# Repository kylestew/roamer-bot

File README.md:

# roamer-bot

A small robotics learning platform built on the Pololu Romi chassis.

The current direction is a custom-core Studio Mission Rover: Romi chassis, custom MCU + motor-control PCB, laptop tether first, telemetry from day one, and no ROS in the core system until the low-level robot is understood.

# Current Direction

The project is moving from the original Romi 32U4 + Raspberry Pi + ROS approach toward a custom-core learning build:

- Treat the old implementation as historical/reference material.
- Use the Romi chassis as the mechanical target.
- Build a custom MCU + motor-control PCB that replaces the purchasable Pololu Romi control board.
- Keep the first version tethered to a laptop.
- Capture telemetry from day one.
- Keep ROS out of the core system until the custom board, telemetry, and motor-control loop are understood.

# Current Structure

- `hardware/`: active Rev A PCB and mechanical-constraint work.
- `firmware/`: active custom MCU firmware work.
- `host/`: active laptop tether, telemetry capture, and test tooling work.
- `legacy/old-romi/`: previous Romi 32U4 + Raspberry Pi + ROS implementation, kept only as reference.
- `docs/`: datasheets, Romi reference assets, and legacy dependency references.

# Planning

- [Hardware design, release gate, and Rev B plan](hardware/README.md)
- [Studio Mission Rover roadmap](STUDIO_MISSION_ROVER_ROADMAP.md)
- [TO BUY list](TO_BUY.md)
- [Legacy Romi references](docs/legacy-romi-references.md)

# First Milestone

Teleop + encoder logging + safe stop:

- Command left and right motors from a laptop or simple host.
- Read left and right encoder counts.
- Stream basic telemetry.
- Stop motors on command timeout.
- Save a short bench or floor test log on the host.

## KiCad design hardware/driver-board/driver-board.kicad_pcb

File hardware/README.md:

# Roamer Hardware

Status: **Rev A was ordered from JLCPCB on 2026-07-18 and is in production; fabrication and bring-up verification remain.**

This is the single source of truth for the custom Romi motor-controller hardware. If this document disagrees with the KiCad design, the schematic, PCB, and generated BOM are authoritative and this document must be corrected.

## Objective

Rev A replaces the Pololu Romi controller for the minimum useful rover loop:

- independently command two brushed DC motors;
- count both quadrature encoders in hardware;
- communicate with a laptop over native USB;
- report battery, motion, timeout, and reset state;
- stop both motors safely when commands cease; and
- mount directly to the Romi chassis and encoder boards.

Rev A is intentionally a focused learning board. It does not include an IMU, Raspberry Pi interface or power supply, wireless, charging, a 5 V accessory rail, or a polished multi-source power system.

Success means teleoperation, reliable encoder logging, useful telemetry, and an unconditional command-timeout stop during a short bench or floor run.

## Design Files

- [Top-level schematic](driver-board/driver-board.kicad_sch)
- [Power sheet](driver-board/power.kicad_sch)
- [Motor-control sheet](driver-board/motor_control.kicad_sch)
- [USB sheet](driver-board/usb.kicad_sch)
- [PCB](driver-board/driver-board.kicad_pcb)
- [KiCad project](driver-board/driver-board.kicad_pro)
- [Generated BOM snapshot](driver-board/driver-board.csv)
- [Rev A JLCPCB manufacturing release](releases/rev-a-jlcpcb-2026-07-18.md)
- [Custom footprints](driver-board/CustomParts.pretty/)

The checked-in CSV is a working snapshot, not purchase-ready assembly data. Regenerate and review the BOM and placement file from the final schematic and PCB immediately before ordering.

## Rev A Architecture

### Battery and power

Rev A is designed only for the Romi six-AA bay populated with rechargeable NiMH cells:

- nominal pack voltage: approximately 7.2 V;
- fresh-pack voltage: approximately 8.4 V;
- bench-supply ceiling: 8.5 V; and
- alkaline cells are prohibited because a fresh pack can approach 9.6 V, reducing DRV8838 transient margin and increasing motor stall current beyond the intended operating envelope.

The implemented load-current path is:

```text
BT1+ -> VBAT -> F1 -> Q1 -> VBAT_SAFE -> Q2 -> VBAT_SW
BT1- -> BT2+
BT2- -> GND
```

- F1 is a Littelfuse `MINISMDC260F/16-2` resettable PTC: 16 V, 2.6 A hold, 5 A trip.
- Q1 (`AO3401A`) provides reverse-battery protection.
- Q2 (`AO4407A`) is the high-side whole-board power MOSFET.
- SW2 (`SK-3296S-01-L2`) switches Q2's gate; it does not carry motor or regulator load current.
- `VBAT_SW` feeds both motor-driver VM inputs, both encoder boards, and the 3.3 V buck regulator.
- USB VBUS is used only around the USB interface. It does not power `+3V3`, the encoders, or the motors.

The LMR51430 buck, 5.6 uH L1, and output network generate approximately 3.3 V from `VBAT_SW`. There is no 5 V logic rail, separate `+3V3A` rail, or analog-rail inductor. VDDA is fed directly from `+3V3` with local 10 nF and 1 uF decoupling.

Battery telemetry uses a 100 kOhm / 33 kOhm divider into PB0/ADC1_IN8. Rev A deliberately omits a filter capacitor; firmware must use a long ADC sample time and modest averaging. This is approximate state telemetry, not precision fuel gauging.

### Motor power and protection

Rev A uses one TI DRV8838 per motor. The target motor is the Pololu #1520 120:1 high-power mini plastic gearmotor, specified around 3-6 V with approximately 1.25 A stall current at 4.5 V.

Normal firmware output is capped at 75% absolute PWM duty, following the Pololu Romi operating policy. Full-duty operation is diagnostic-only, with a current-limited supply and explicit test firmware.

Motor-rail capacitance is:

| Driver | VM high-frequency bypass | VM local storage | VCC bypass |
| --- | --- | --- | --- |
| U3, left | C11, 100 nF | C10, 10 uF | C12, 100 nF |
| U4, right | C14, 100 nF | C13, 10 uF | C15, 100 nF |

C16 is a shared 220 uF, 25 V bulk capacitor across `VBAT_SW` and GND. It buffers short current steps and returned energy but does not replace the battery as the sustained current source. Rev A has no TVS or characterized regenerative clamp; startup, stop, reversal, stall-release, and power-off peaks must be measured during bring-up.

Each DRV8838 `nSLEEP` input has a hardware pulldown. Firmware must also initialize `nSLEEP`, PWM/EN, and PH to disabled states before accepting commands. A host timeout, watchdog event, low-battery condition, or unsafe state commands PWM to zero and puts the drivers to sleep while the MCU remains powered.

DRV8838 provides no fault or current-sense output. Diagnose problems through commanded state, encoder response, battery voltage, reset cause, temperature, and measured supply waveforms.

### Motor and encoder connectors

The encoder boards are powered from `VBAT_SW` because their specified VCC range begins above 3.3 V. Their A/B outputs are open-drain and pulled up to `+3V3`, so the STM32 receives safe 3.3 V logic. Firmware must treat encoder counts as unreliable when the battery approaches the encoder's 3.5 V minimum plus margin.

Viewed from the top of the PCB:

| Connector | Top-to-bottom pin order |
| --- | --- |
| J4, left | `GND`, `ENC_L_A`, `ENC_L_B`, `VBAT_SW`, `ML+`, `ML-` |
| J3, right | `MR-`, `MR+`, `VBAT_SW`, `ENC_R_A`, `ENC_R_B`, `GND` |

The right connector is intentionally mirrored for cleaner symmetric routing and does not reproduce the Pololu silkscreen order. Confirm actual wheel-forward polarity and encoder count sign during bring-up; correct direction convention in firmware rather than casually changing the verified connector layout.

### MCU and firmware-facing pin contract

U1 is an `STM32F103CBT6` in LQFP-48 with a 16 MHz HSE crystal, native USB FS, SWD, two hardware encoder timers, two PWM channels, and battery ADC input.

| Function | MCU pin | Peripheral or mode |
| --- | --- | --- |
| Heartbeat LED | PC13 | GPIO, active-low |
| Left sleep | PB12 | GPIO, active-low |
| Left direction | PB13 | GPIO |
| Left PWM | PB14 | TIM1 CH2N |
| Right sleep | PB5 | GPIO, active-low |
| Right direction | PB6 | GPIO |
| Right PWM | PB7 | TIM4 CH2 |
| Left encoder A/B | PA6 / PA7 | TIM3 CH1 / CH2 |
| Right encoder A/B | PB3 / PA15 | TIM2 CH2 / CH1, partial remap 1 |
| Battery level | PB0 | ADC1 IN8 |
| USB D-/D+ | PA11 / PA12 | USB FS |
| SWDIO/SWCLK | PA13 / PA14 | SWD; SWO is not connected |

The MCU contains I2C2 on PB10/PB11, but those package pins are explicit no-connects on Rev A. There are no pullups, connector, or sensor footprint, so Rev A has no usable I2C bus. Remove the stale I2C2 assignment from the CubeMX design artifact before release. User buttons and additional controlled status LEDs are also deferred; Rev A has reset, a power LED, and one MCU heartbeat/status LED.

SWD is the primary programming and recovery path. The 1.27 mm 2x5 header exposes target power, GND, SWDIO, SWCLK, and NRST; the target supplies its own 3.3 V.

### USB policy

J2 is a USB-C USB 2.0 receptacle with 5.1 kOhm CC resistors and USBLC6-2 ESD protection. D+/D- run directly to the STM32 without external series resistors and are routed via-free on `F.Cu` over the solid ground plane.

Rev A is battery-powered and USB-data-only:

- USB alone leaves the board off.
- Battery/bench power with USB disconnected supports standalone operation.
- Battery/bench power plus USB supports programming, commands, and telemetry without backfeeding the board from VBUS.

R5 permanently enables the external D+ pullup whenever board 3.3 V is present; attachment is not gated by VBUS. Rev A therefore assumes connection to an already-powered host. If enumeration fails after connection to an unpowered or booting host, unplugging and reconnecting USB is the accepted recovery. Add VBUS sensing and pullup gating in Rev B if reliable or standards-compliant self-powered attachment is required.

## PCB and Manufacturing Policy

Rev A is a four-layer, approximately 1.6 mm FR-4 board:

| Layer | Primary use |
| --- | --- |
| `F.Cu` | Components, signals, short local power pours, and regulator switching loops |
| `In1.Cu` | Continuous GND plane; never split into motor and logic grounds |
| `In2.Cu` | `VBAT_SW` and `+3V3` power distribution |
| `B.Cu` | Lower-speed signals plus a stitched GND fill |

Rules to preserve:

- Keep USB, clocks, feedback, ADC, reset, and other sensitive signals over continuous ground.
- Do not route a bottom-layer signal across an `In2.Cu` power split without a same-layer or otherwise continuous return reference.
- Keep the U5 VIN, bootstrap, switch-node, inductor, output-capacitor, and feedback loops compact.
- Keep motor-current paths and returns short and broad, with multiple vias where current changes layers.
- Keep the DRV8838 exposed-pad solder areas free of drilled holes. The implemented nearby ordinary GND vias require no via-in-pad fill or cap process.
- Keep motor current away from encoder, USB, crystal, reset, SWD, and BATLEV routing.

The smallest intentional signal vias are 0.55 mm diameter with a 0.25 mm drill. These are within JLCPCB rigid-board capability and have a 0.15 mm radial annular ring. Continue to use 0.70/0.30 mm or larger vias for high-current, thermal, and principal ground paths when space permits.

Silkscreen is front-side only. The board includes assembly and connector labels, polarity and pin-1 marks, test-point labels, board/battery identification, and the capybara artwork. There is no back silkscreen.

Mechanical fit has been checked repeatedly against the Romi chassis, encoder boards, battery contacts, wheels, clips, ribs, caster area, mounting holes, switch access, and USB cable access. Preserve the verified board outline and chassis-critical footprints.

## Current Verification State

As of 2026-07-21:

- JLCPCB order `W2026071807372374` is in production and its PCB production file is confirmed;
- the order contains five PCBs, including two economically assembled PCBAs;
- fabrication completion and physical bring-up remain;
- schematic ERC: **0 violations**;
- PCB DRC: **0 violations**;
- PCB connectivity: **0 unconnected items**;
- SW2 SMD-anchor pad semantics and silkscreen clearances are fixed in both the library footprint and board instance; and
- top, bottom, and isometric views plus a 1:1 chassis comparison have been reviewed.

The KiCad project intentionally excludes several generic checks, including missing courtyards, track endpoints not centered on vias, tuning-profile geometry, footprint filters, and footprint type. A clean report means the active Rev A rule set passes; it does not replace the fabrication preview and manual checks below.

## Fabrication Release Gate

Complete every item before ordering:

- [ ] Remove the unusable I2C2 PB10/PB11 assignment from the CubeMX artifact and keep I2C, user buttons, and extra LEDs explicitly deferred to Rev B.
- [ ] Refill all zones, complete the final GND-stitching pass, and confirm no isolated copper islands.
- [ ] Rerun ERC and PCB DRC with schematic parity, warnings, exclusions, and zero unconnected items reviewed.
- [ ] Reinspect the complete power path, battery series link, Q1/Q2 orientation, both driver VM/output/ground loops, U5 layout, USB routing, NRST, BOOT0, oscillator, and MCU decoupling.
- [ ] Verify both `nSLEEP` pulldowns hold the drivers off during reset, boot, SWD attach, unpowered-MCU states, and firmware initialization.
- [ ] Verify BATLEV stability with motors and the buck switching; accept the unfiltered divider only if firmware sampling is adequate.
- [ ] Confirm the actual JLCPCB stackup and USB geometry, drill and slot sizes, annular rings, mask dams, copper-edge clearance, and silkscreen capability.
- [ ] Regenerate the BOM and CPL/position data from the final design.
- [ ] Fill or explicitly waive every missing JLCPCB field, especially C22, C23, R5, R12, R13, and R16-R19.
- [ ] Manually verify U1, U3/U4, U5, F1, Q1, Q2, SW2, J2, J3/J4, L1, C16, and C17-C21 against current value, package, polarity, voltage/current rating, lifecycle, and stock.
- [ ] Review Gerbers, drills, IPC netlist, BOM, and CPL independently, then inspect the JLCPCB fabrication and assembly previews for side, rotation, pin 1, polarity, DNP state, and footprint alignment.
- [ ] Archive the exact schematic, PCB, fabrication outputs, BOM, CPL, and firmware revision used for the build.

Useful release commands:

```sh
/Applications/KiCad/KiCad.app/Contents/MacOS/kicad-cli sch erc \
  --severity-all hardware/driver-board/driver-board.kicad_sch

/Applications/KiCad/KiCad.app/Contents/MacOS/kicad-cli pcb drc \
  --schematic-parity --severity-all \
  hardware/driver-board/driver-board.kicad_pcb
```

## Bring-Up Plan

1. Inspect polarity, orientation, shorts, solder joints, and the unpowered resistance of each rail.
2. Use a current-limited bench supply at a low voltage with motors disconnected; verify `VBAT`, `VBAT_SAFE`, `VBAT_SW`, and `+3V3` in order.
3. Verify SW2/Q2 behavior, Q1 reverse protection, no USB backfeed, and USB-only board-off behavior.
4. Attach SWD, confirm NRST/BOOT behavior, program the safe image, and prove both `nSLEEP` inputs and PWM outputs remain inactive through reset and debugger attach.
5. Confirm the 16 MHz HSE/48 MHz system clock, heartbeat LED, USB enumeration, battery ADC reading, and reset-cause telemetry.
6. Connect one motor and its encoder. Start at low duty, verify direction/count sign, sweep duty conservatively, and test timeout stop.
7. Repeat for the other motor, then operate both together while checking encoder integrity and the 3.3 V rail.
8. With a short oscilloscope ground spring, capture `VBAT_SW` at C16 and each driver during start, stop, reversal, simultaneous start, stall release, and power-off at nominal and fresh-pack voltage.
9. Check the PTC, MOSFETs, regulator, inductor, motor drivers, connectors, and C16 temperature during an extended test.
10. Run low-speed straight, turn, stop, and host-disconnect floor tests while saving telemetry.

Bring-up passes when both motors operate independently in both directions, encoder counts remain clean, PWM response is monotonic, command timeout and watchdog stop the motors, USB remains stable, and motor events do not reset the MCU or violate measured rail margins.

Record Rev A current, voltage transients, temperatures, resets, encoder errors, mechanical fit, and USB behavior. Those measurements—not guesses—select Rev B protection and power changes.

## Critical Parts

| Function | Part | Current JLCPCB/LCSC ID |
| --- | --- | --- |
| MCU | STM32F103CBT6 | C8304 |
| Motor drivers | DRV8838, U3/U4 | C86667 |
| Buck regulator | LMR51430XDDCR | C5185863 |
| Buck inductor | SWPA8065S5R6MT, 5.6 uH | C96977 |
| USB ESD | USBLC6-2SC6 | C7519 |
| USB-C connector | GT-USB-7010ASV | C2988369 |
| Input PTC | MINISMDC260F/16-2 | C16490 |
| Reverse-protection MOSFET | AO3401A | C15127 |
| Power MOSFET | AO4407A | C16072 |
| Power switch | SK-3296S-01-L2 | C500051 |
| Bulk capacitor | 220 uF, 25 V | C190724 |
| HSE crystal | 16 MHz, 3225 | C13738 |

Recheck every ID and stock state at order time; this table records the design, not a sourcing guarantee.

## Rev B Backlog

Rev B begins only after Rev A assembly and measured testing. Priorities are:

1. Correct every demonstrated Rev A electrical, mechanical, sourcing, or firmware-contract defect.
2. Retain USB and add a 3.3 V UART host interface; keep motor safety, encoder counting, timeout, and low-level control on the STM32.
3. Add a 6-axis IMU and an isolatable 3.3 V I2C/Qwiic-style sensor connector.
4. Consider an unpopulated Pi-compatible header, but default to a separately powered host sharing only communications and GND. Do not advertise HAT compatibility without meeting the complete specification.
5. Add VBUS sensing and gated USB attachment; optionally support USB/host-powered logic while guaranteeing the motor rail remains off and no source can backfeed another.
6. Add snubber, clamp/TVS, distributed bulk-capacitance, current-sense, or fault-reporting provisions only where Rev A measurements justify them.
7. Consider a diagnostic motor driver such as DRV8213 and a newer MCU such as STM32G0B1 only if Rev A exposes a concrete limitation.
8. Do not add a magnetometer beside motors or an unrestricted multi-amp Pi supply by default. Remote magnetic sensing and host power require explicit mechanical and power requirements.

Any host reset, disconnect, or brownout must still cause the STM32 watchdog to stop the motors safely.

## References and Asset Provenance

Local vendor references retained as primary sources:

- [STM32F103 datasheet](docs/stm32f103c8.pdf)
- [DRV8838 datasheet](docs/drv8838.pdf)
- [LMR51430 datasheet](docs/lmr51430.pdf)
- [AO4407A / C16072 reference](docs/C16072.pdf)
- [SK-3296S-01-L2 / C500051 reference](docs/C500051.pdf)
- [Reset switch / C720477 reference](docs/C720477.pdf)
- [Alternate switch / C1788495 reference](driver-board/datasheets/C1788495.pdf), not fitted on current Rev A

External design references:

- [Pololu Romi 32U4 control-board guide](https://www.pololu.com/docs/0J69/all)
- [Pololu Romi 32U4 resources](https://www.pololu.com/product/3544/resources)
- [Pololu #1520 motor](https://www.pololu.com/product/1520)
- [Pololu Romi encoder pair](https://www.pololu.com/product/3542)
- [ST USB hardware and PCB guidelines, AN4879](https://www.st.com/resource/en/application_note/an4879-introduction-to-usb-hardware-and-pcb-guidelines-using-stm32-mcus-stmicroelectronics.pdf)
- [Samsung CL21A106KAYNNNE data](https://product.samsungsem.com/mlcc/CL21A106KAYNNN.do)
- [Raspberry Pi hardware documentation](https://www.raspberrypi.com/documentation/computers/raspberry-pi.html)

3D-model provenance:

- `driver-board/3dmodels/GT-USB-7010ASV.step` comes from the GPL-2.0-licensed [MiSTerLaggy_MiSTer hardware repository](https://github.com/MiSTer-devel/MiSTerLaggy_MiSTer/blob/main/hardware/GT-USB-7010ASV.step).
- `driver-board/3dmodels/SK-3296S-01-L2.wrl` was converted without changing millimetre-scale alignment from the [EasyEDA model](https://modules.easyeda.com/3dmodel/a3deeb560a8c4467ab29e6daf75b62b9) for [LCSC C500051](https://www.lcsc.com/product-detail/Electrical-Switches_XKB-Connectivity-SK-3296S-01-L2_C500051.html).

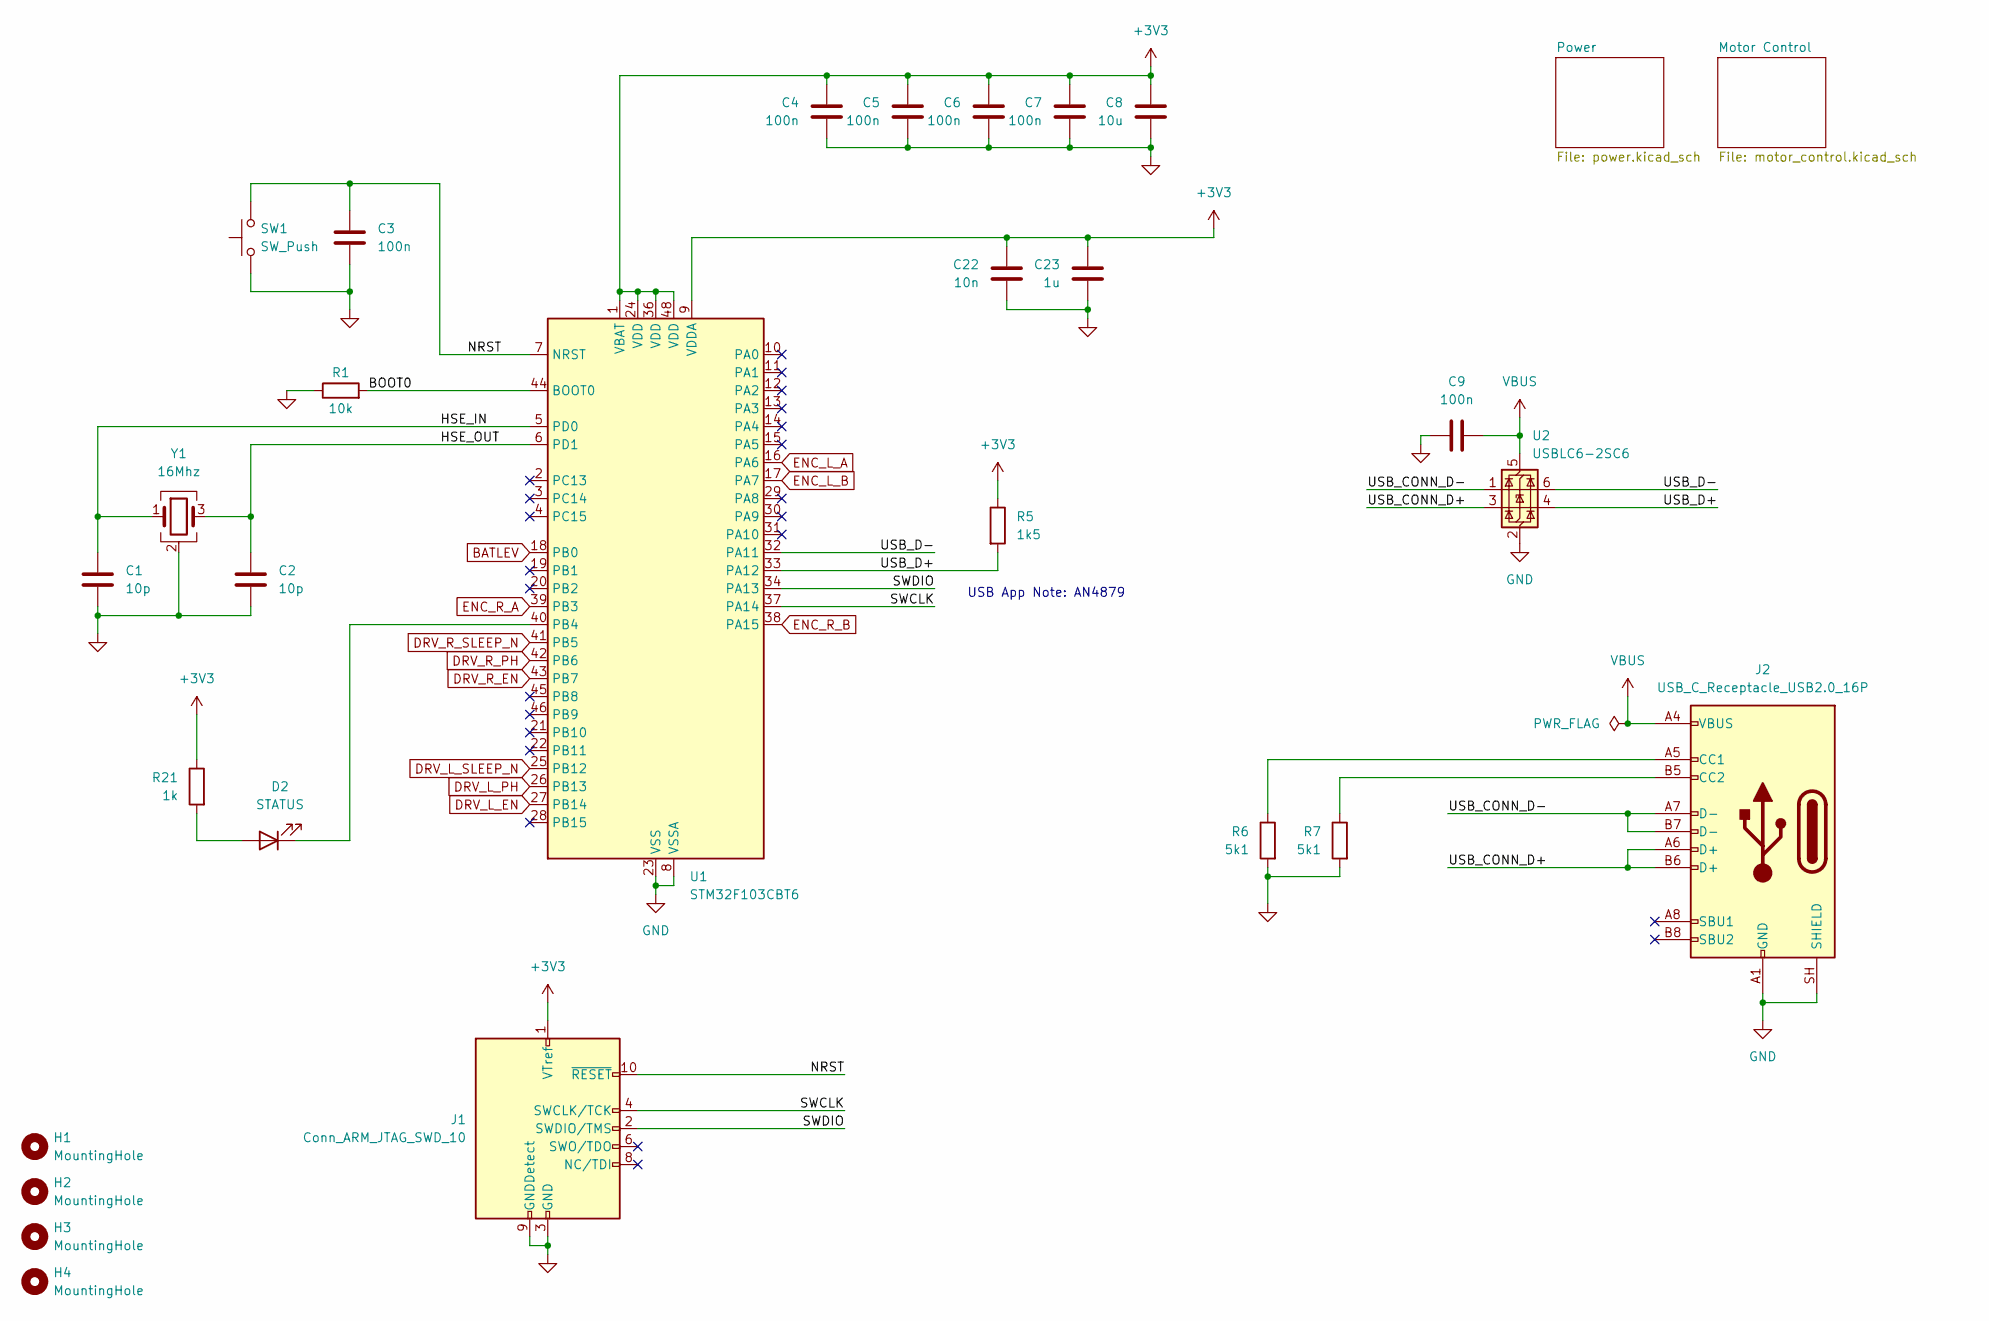
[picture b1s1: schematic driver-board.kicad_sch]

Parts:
C1, C2: 10p; C_0402_1005Metric; JLCPCB C32949
C3, C4, C5, C6, C7, C9: 100n; C_0402_1005Metric; JLCPCB C307331
C8: 10u; C_0805_2012Metric; JLCPCB C15850
C22: 10n; C_0402_1005Metric; JLCPCB C15195
C23: 1u; C_0603_1608Metric; JLCPCB C15849
D2: STATUS; LED_0805_2012Metric; JLCPCB C2297
H1, H2, H3, H4: MountingHole; MountingHole_2.3mm_2-56
J1: Conn_ARM_JTAG_SWD_10; PinHeader_2x05_P1.27mm_Vertical_SMD; JLCPCB C2932107
J2: USB_C_Receptacle_USB2.0_16P; USB_C_Receptacle_G-Switch_GT-USB-7010ASV; JLCPCB C2988369
R1: 10k; R_0402_1005Metric; MPN 0603WAF1002T5E; JLCPCB C25744
R5: 1k5; R_0402_1005Metric; JLCPCB C25867
R6, R7: 5k1; R_0402_1005Metric; JLCPCB C25905
R21: 1k; R_0603_1608Metric; JLCPCB C21190
SW1: SW_Push; SW_SPST_TS-1088-xR020; JLCPCB C720477
U1: STM32F103CBT6; LQFP-48_7x7mm_P0.5mm; JLCPCB C8304
U2: USBLC6-2SC6; SOT-23-6; JLCPCB C7519
Y1: 16Mhz; Crystal_SMD_3225-4Pin_3.2x2.5mm; JLCPCB C13738

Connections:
+3V3: C4.1, C5.1, C6.1, C7.1, C8.1, C22.1, C23.1, J1.1 (VTref), R5.1, R21.1, U1.1 (VBAT), U1.9 (VDDA), U1.24 (VDD), U1.36 (VDD), U1.48 (VDD); also elsewhere on the board
/BOOT0: R1.2, U1.44 (BOOT0)
/HSE_IN: C1.1, U1.5 (PD0), Y1.1
/HSE_OUT: C2.1, U1.6 (PD1), Y1.3
/NRST: C3.2, J1.10 (~RESET), SW1.2, U1.7 (NRST)
/SWCLK: J1.4 (SWCLK/TCK), U1.37 (PA14)
/SWDIO: J1.2 (SWDIO/TMS), U1.34 (PA13)
/USB_CONN_D+: J2.A6 (D+), J2.B6 (D+), U2.3 (I/O2)
/USB_CONN_D-: J2.A7 (D-), J2.B7 (D-), U2.1 (I/O1)
/USB_D+: R5.2, U1.33 (PA12), U2.4 (I/O2)
/USB_D-: U1.32 (PA11), U2.6 (I/O1)
BATLEV: U1.18 (PB0); also elsewhere on the board
DRV_L_EN: U1.27 (PB14); also elsewhere on the board
DRV_L_PH: U1.26 (PB13); also elsewhere on the board
DRV_L_SLEEP_N: U1.25 (PB12); also elsewhere on the board
DRV_R_EN: U1.43 (PB7); also elsewhere on the board
DRV_R_PH: U1.42 (PB6); also elsewhere on the board
DRV_R_SLEEP_N: U1.41 (PB5); also elsewhere on the board
ENC_L_A: U1.16 (PA6); also elsewhere on the board
ENC_L_B: U1.17 (PA7); also elsewhere on the board
ENC_R_A: U1.39 (PB3); also elsewhere on the board
ENC_R_B: U1.38 (PA15); also elsewhere on the board
GND: C1.2, C2.2, C3.1, C4.2, C5.2, C6.2, C7.2, C8.2, C9.2, C22.2, C23.2, J1.3 (GND), J1.5 (GND), J1.9 (GNDDetect), J2.A1 (GND), J2.A12 (GND), J2.B1 (GND), J2.B12 (GND), J2.SH (SHIELD), R1.1, R6.2, R7.2, SW1.1, U1.8 (VSSA), U1.23 (VSS), U1.35 (VSS), U1.47 (VSS), U2.2 (GND), Y1.2 (G), Y1.4 (G); also elsewhere on the board
unnamed: D2.2 (A), R21.2
unnamed: D2.1 (K), U1.40 (PB4)
unnamed: J2.A5 (CC1), R6.1
unnamed: J2.B5 (CC2), R7.1
VBUS: C9.1, J2.A4 (VBUS), J2.A9 (VBUS), J2.B4 (VBUS), J2.B9 (VBUS), U2.5 (VBUS)

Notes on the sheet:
USB App Note: AN4879

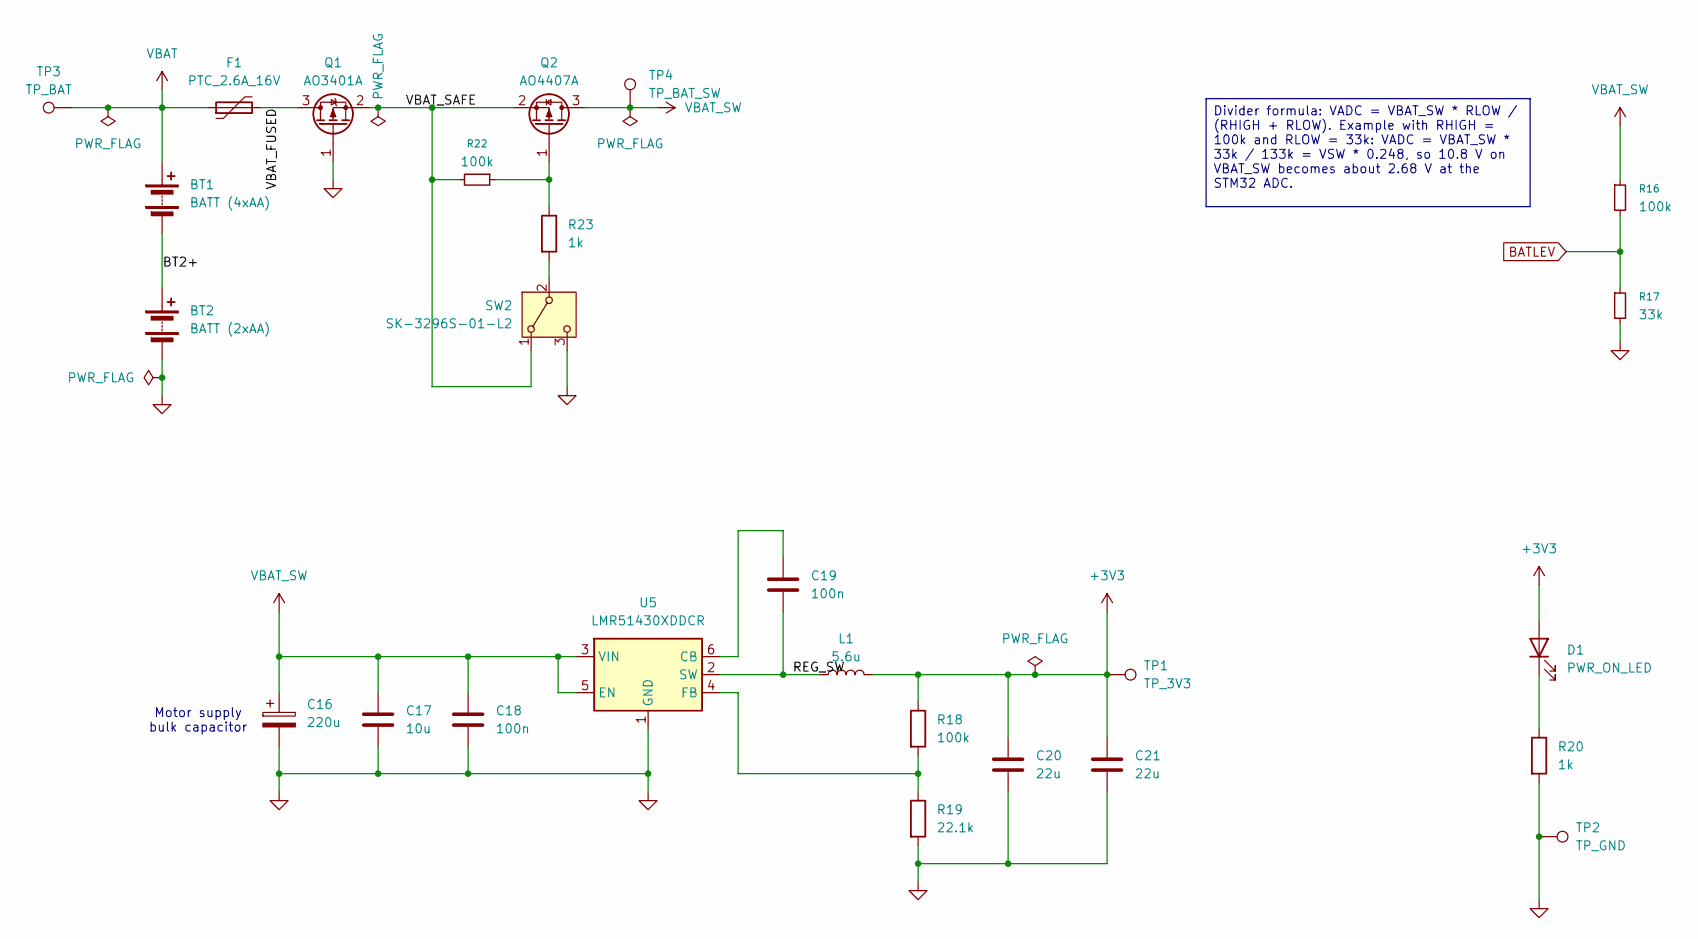
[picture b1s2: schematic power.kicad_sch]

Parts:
BT1: BATT (4xAA); Romi_Chassis_BatteryContactPair_2Slot_14_50mm
BT2: BATT (2xAA); Romi_Chassis_BatteryContactPair_2Slot_14_50mm
C16: 220u; CP_Elec_6.3x7.7; JLCPCB C190724
C17: 10u; C_0805_2012Metric; JLCPCB C15850
C18, C19: 100n; C_0402_1005Metric; JLCPCB C307331
C20, C21: 22u; C_1206_3216Metric; JLCPCB C12891
D1: PWR_ON_LED; LED_0603_1608Metric; JLCPCB C2286
F1: PTC_2.6A_16V; Fuse_1812_4532Metric; JLCPCB C16490
L1: 5.6u; L_APV_ANR8065; JLCPCB C96977
Q1: AO3401A; SOT-23; JLCPCB C15127
Q2: AO4407A; AO4407A_SO-8_GSD; JLCPCB C16072
R16, R18: 100k; R_0402_1005Metric; JLCPCB C25741
R17: 33k; R_0402_1005Metric; JLCPCB C25779
R19: 22.1k; R_0402_1005Metric; JLCPCB C43473
R20, R23: 1k; R_0603_1608Metric; JLCPCB C21190
R22: 100k; R_0603_1608Metric; JLCPCB C25803
SW2: SK-3296S-01-L2; SW_SPDT_RightAngle_XKB_SK-3296S-01-L2; JLCPCB C500051
TP1: TP_3V3; TestPoint_Pad_2.0x2.0mm
TP2: TP_GND; TestPoint_Pad_2.0x2.0mm
TP3: TP_BAT; TestPoint_Pad_2.0x2.0mm
TP4: TP_BAT_SW; TestPoint_Pad_2.0x2.0mm
U5: LMR51430XDDCR; SOT-23-6; JLCPCB C5185863

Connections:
+3V3: C20.1, C21.1, D1.2 (A), L1.2, R18.1, TP1.1 (1_1); also elsewhere on the board
/Power/BT2+: BT1.2 (-), BT2.1 (+)
/Power/REG_SW: C19.2, L1.1, U5.2 (SW)
/Power/VBAT_FUSED: F1.2, Q1.3 (D)
/Power/VBAT_SAFE: Q1.2 (S), Q2.2 (S), R22.2, SW2.1 (A)
BATLEV: R16.2, R17.1; also elsewhere on the board
GND: BT2.2 (-), C16.2, C17.2, C18.2, C20.2, C21.2, Q1.1 (G), R17.2, R19.2, R20.2, SW2.3 (C), TP2.1 (1_1), U5.1 (GND); also elsewhere on the board
unnamed: D1.1 (K), R20.1
unnamed: Q2.1 (G), R22.1, R23.1
unnamed: R23.2, SW2.2 (B)
unnamed: C19.1, U5.6 (CB)
unnamed: R18.2, R19.1, U5.4 (FB)
VBAT: BT1.1 (+), F1.1, TP3.1 (1_1)
VBAT_SW: C16.1, C17.1, C18.1, Q2.3 (D), R16.1, TP4.1 (1_1), U5.3 (VIN), U5.5 (EN); also elsewhere on the board

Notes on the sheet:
Motor supply bulk capacitor
Divider formula: VADC = VBAT_SW * RLOW / (RHIGH + RLOW). Example with RHIGH = 100k and RLOW = 33k: VADC = VBAT_SW * 33k / 133k = VSW * 0.248, so 10.8 V on VBAT_SW becomes about 2.68 V at the STM32 ADC.

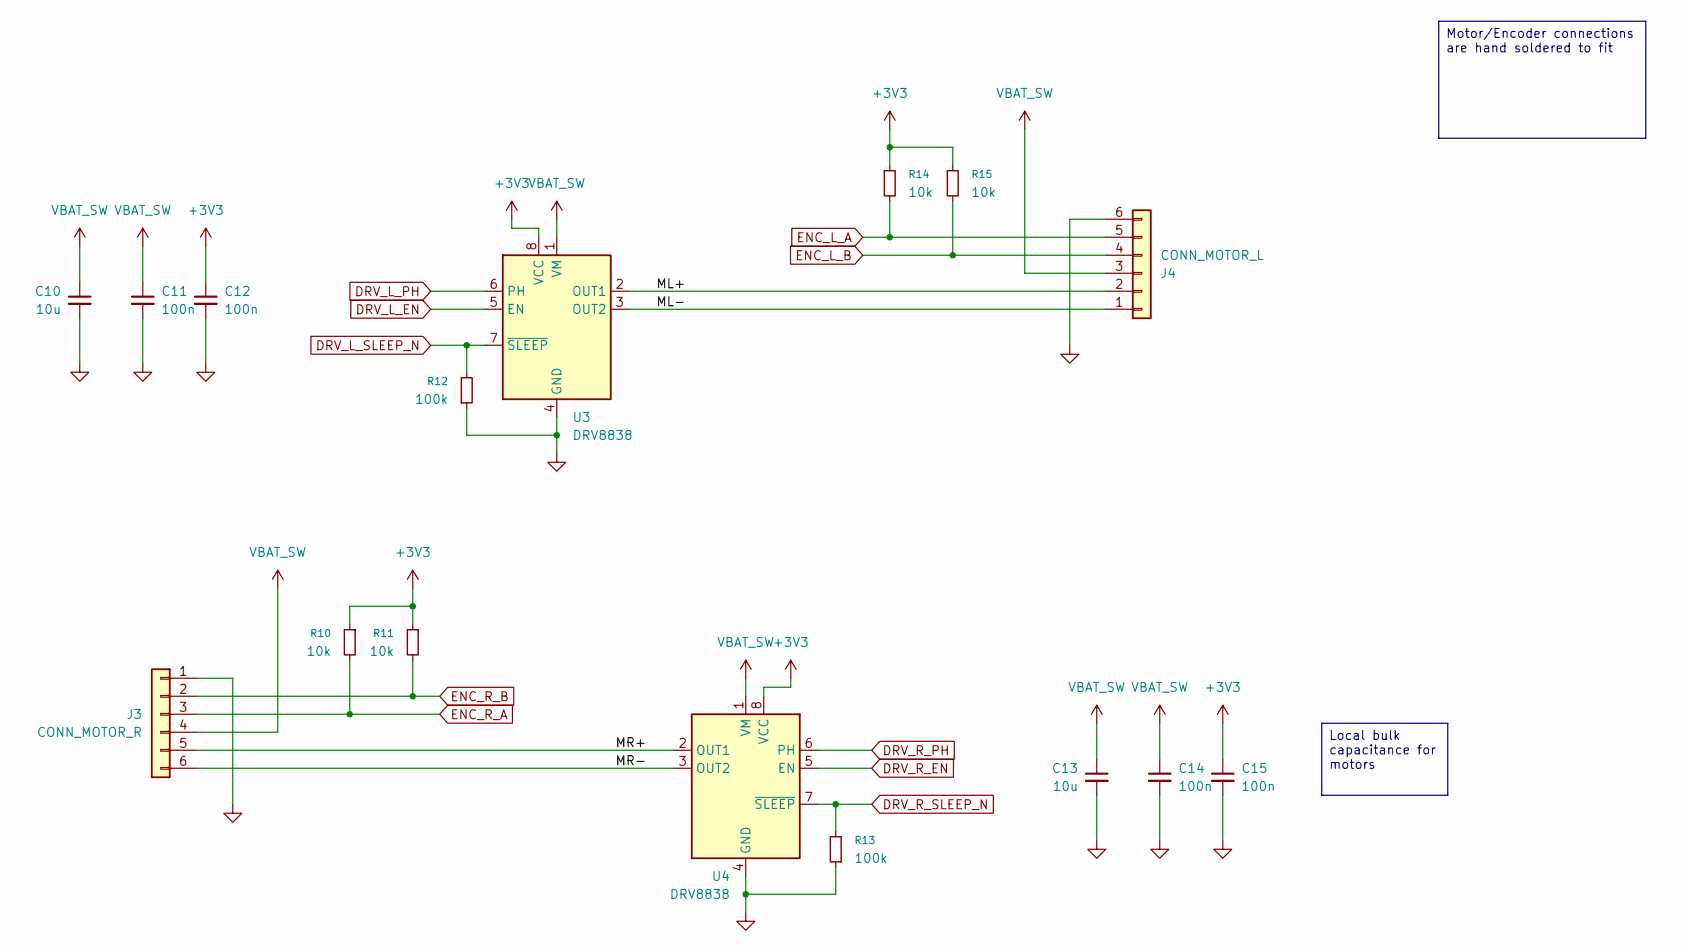
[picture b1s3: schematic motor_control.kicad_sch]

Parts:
C10, C13: 10u; C_0805_2012Metric; JLCPCB C15850
C11, C12, C14, C15: 100n; C_0402_1005Metric; JLCPCB C307331
J3: CONN_MOTOR_R; PinSocket_1x06_P2.54mm_Vertical
J4: CONN_MOTOR_L; PinSocket_1x06_P2.54mm_Vertical
R10, R11, R14, R15: 10k; R_0402_1005Metric; JLCPCB C25744
R12, R13: 100k; R_0402_1005Metric; JLCPCB C25741
U3, U4: DRV8838; WSON-8-1EP_2x2mm_P0.5mm_EP0.9x1.6mm; JLCPCB C86667

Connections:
+3V3: C12.1, C15.1, R10.1, R11.1, R14.1, R15.1, U3.8 (VCC), U4.8 (VCC); also elsewhere on the board
/Motor Control/ML+: J4.2, U3.2 (OUT1)
/Motor Control/ML-: J4.1, U3.3 (OUT2)
/Motor Control/MR+: J3.5, U4.2 (OUT1)
/Motor Control/MR-: J3.6, U4.3 (OUT2)
DRV_L_EN: U3.5 (EN); also elsewhere on the board
DRV_L_PH: U3.6 (PH); also elsewhere on the board
DRV_L_SLEEP_N: R12.2, U3.7 (~SLEEP); also elsewhere on the board
DRV_R_EN: U4.5 (EN); also elsewhere on the board
DRV_R_PH: U4.6 (PH); also elsewhere on the board
DRV_R_SLEEP_N: R13.2, U4.7 (~SLEEP); also elsewhere on the board
ENC_L_A: J4.5, R14.2; also elsewhere on the board
ENC_L_B: J4.4, R15.2; also elsewhere on the board
ENC_R_A: J3.3, R10.2; also elsewhere on the board
ENC_R_B: J3.2, R11.2; also elsewhere on the board
GND: C10.2, C11.2, C12.2, C13.2, C14.2, C15.2, J3.1, J4.6, R12.1, R13.1, U3.4 (GND), U3.9 (GND), U4.4 (GND), U4.9 (GND); also elsewhere on the board
VBAT_SW: C10.1, C11.1, C13.1, C14.1, J3.4, J4.3, U3.1 (VM), U4.1 (VM); also elsewhere on the board

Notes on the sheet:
Motor/Encoder connections are hand soldered to fit
Local bulk capacitance for motors

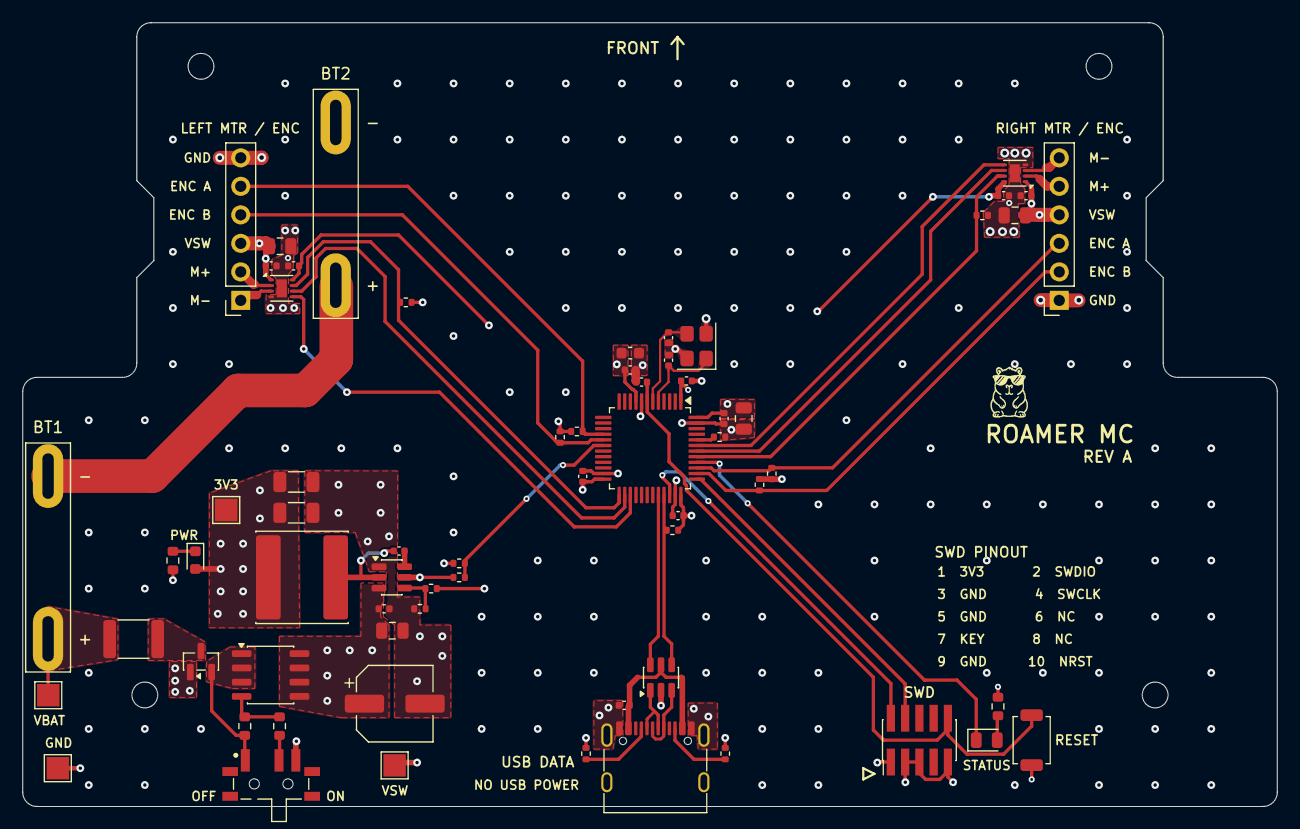
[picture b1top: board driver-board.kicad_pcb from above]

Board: 4 copper layers, 111.8 x 69.8 mm, 70 parts (0 on the bottom side), 43 nets.

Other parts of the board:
G1: CAPYBARA_ARTWORK; Capybara_Sunglasses

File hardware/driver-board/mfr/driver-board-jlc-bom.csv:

Comment,Designator,Footprint,JLCPCB Part #（optional）
10p,"C1,C2",Capacitor_SMD:C_0402_1005Metric,C32949
100n,"C3,C4,C5,C6,C7,C9,C11,C12,C14,C15,C18,C19",Capacitor_SMD:C_0402_1005Metric,C307331
10u,"C8,C10,C13,C17",Capacitor_SMD:C_0805_2012Metric,C15850
220u,C16,Capacitor_SMD:CP_Elec_6.3x7.7,C190724
22u,"C20,C21",Capacitor_SMD:C_1206_3216Metric,C12891
10n,C22,Capacitor_SMD:C_0402_1005Metric,C15195
1u,C23,Capacitor_SMD:C_0603_1608Metric,C15849
PWR_ON_LED,D1,LED_SMD:LED_0603_1608Metric,C2286
STATUS,D2,LED_SMD:LED_0805_2012Metric,C2297
PTC_2.6A_16V,F1,Fuse:Fuse_1812_4532Metric,C16490
Conn_ARM_JTAG_SWD_10,J1,Connector_PinHeader_1.27mm:PinHeader_2x05_P1.27mm_Vertical_SMD,C2932107
USB_C_Receptacle_USB2.0_16P,J2,Connector_USB:USB_C_Receptacle_G-Switch_GT-USB-7010ASV,C2988369
5.6u,L1,Inductor_SMD:L_APV_ANR8065,C96977
AO3401A,Q1,Package_TO_SOT_SMD:SOT-23,C15127
AO4407A,Q2,CustomParts:AO4407A_SO-8_GSD,C16072
10k,"R1,R10,R11,R14,R15",Resistor_SMD:R_0402_1005Metric,C25744
1k5,R5,Resistor_SMD:R_0402_1005Metric,C25867
5k1,"R6,R7",Resistor_SMD:R_0402_1005Metric,C25905
100k,"R12,R13,R16,R18",Resistor_SMD:R_0402_1005Metric,C25741
33k,R17,Resistor_SMD:R_0402_1005Metric,C25779
22.1k,R19,Resistor_SMD:R_0402_1005Metric,C43473
1k,"R20,R21,R23",Resistor_SMD:R_0603_1608Metric,C21190
100k,R22,Resistor_SMD:R_0603_1608Metric,C25803
SW_Push,SW1,Button_Switch_SMD:SW_SPST_TS-1088-xR020,C720477
SK-3296S-01-L2,SW2,CustomParts:SW_SPDT_RightAngle_XKB_SK-3296S-01-L2,C500051
STM32F103CBT6,U1,Package_QFP:LQFP-48_7x7mm_P0.5mm,C8304
USBLC6-2SC6,U2,Package_TO_SOT_SMD:SOT-23-6,C7519
DRV8838,"U3,U4",Package_SON:WSON-8-1EP_2x2mm_P0.5mm_EP0.9x1.6mm,C86667
LMR51430XDDCR,U5,Package_TO_SOT_SMD:SOT-23-6,C5185863
16Mhz,Y1,Crystal:Crystal_SMD_3225-4Pin_3.2x2.5mm,C13738

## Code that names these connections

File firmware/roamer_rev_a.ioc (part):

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Mcu.Name=STM32F103C(8-B)Tx
Mcu.Package=LQFP48
Mcu.UserName=STM32F103CBTx
PA11.Mode=Device
PA11.Signal=USB_DM
PA12.Mode=Device
PA12.Signal=USB_DP
PA13.Mode=Serial_Wire
PA13.Signal=SYS_JTMS-SWDIO
PA14.Mode=Serial_Wire
PA14.Signal=SYS_JTCK-SWCLK
PA15.GPIOParameters=GPIO_Label
PA15.GPIO_Label=ENC_R_B
PA15.Signal=S_TIM2_CH1_ETR
PA6.GPIOParameters=GPIO_Label
PA6.GPIO_Label=ENC_L_A
PA6.Signal=S_TIM3_CH1
PA7.GPIOParameters=GPIO_Label
PA7.GPIO_Label=ENC_L_B
PA7.Signal=S_TIM3_CH2
PB0.GPIOParameters=GPIO_Label
PB0.GPIO_Label=BATLEV
PB0.Signal=ADCx_IN8
PB10.GPIOParameters=GPIO_Label
PB10.GPIO_Label=SENSOR_I2C_SCL
PB10.Mode=I2C
PB10.Signal=I2C2_SCL
PB11.GPIOParameters=GPIO_Label
PB11.GPIO_Label=SENSOR_I2C_SDA
PB11.Mode=I2C
PB11.Signal=I2C2_SDA
PB12.GPIOParameters=GPIO_Label,GPIO_OutputLevel
PB12.GPIO_Label=DRV_L_SLEEP_N
PB12.GPIO_OutputLevel=GPIO_PIN_RESET
PB12.Signal=GPIO_Output
PB13.GPIOParameters=GPIO_Label,GPIO_OutputLevel
PB13.GPIO_Label=DRV_L_PH
PB13.GPIO_OutputLevel=GPIO_PIN_RESET
PB13.Signal=GPIO_Output
PB14.GPIOParameters=GPIO_Label
PB14.GPIO_Label=DRV_L_EN
PB14.Signal=S_TIM1_CH2N
PB5.GPIOParameters=GPIO_Label,GPIO_OutputLevel
PB5.GPIO_Label=DRV_R_SLEEP_N
PB5.GPIO_OutputLevel=GPIO_PIN_RESET
PB5.Signal=GPIO_Output
PB3.GPIOParameters=GPIO_Label
PB3.GPIO_Label=ENC_R_A
PB3.Signal=S_TIM2_CH2
PB6.GPIOParameters=GPIO_Label,GPIO_OutputLevel
PB6.GPIO_Label=DRV_R_PH
PB6.GPIO_OutputLevel=GPIO_PIN_RESET
PB6.Signal=GPIO_Output
PB7.GPIOParameters=GPIO_Label
PB7.GPIO_Label=DRV_R_EN
PB7.Signal=S_TIM4_CH2
PC13-TAMPER-RTC.GPIOParameters=GPIO_Label,GPIO_OutputLevel
PC13-TAMPER-RTC.GPIO_Label=LED_HEARTBEAT
PC13-TAMPER-RTC.GPIO_OutputLevel=GPIO_PIN_SET
PC13-TAMPER-RTC.Signal=GPIO_Output
PD0-OSC_IN.Mode=HSE-External-Oscillator
PD0-OSC_IN.Signal=RCC_OSC_IN
PD1-OSC_OUT.Mode=HSE-External-Oscillator
PD1-OSC_OUT.Signal=RCC_OSC_OUT
RCC.HSEDivPLL=RCC_HSE_PREDIV_DIV2
RCC.HSE_VALUE=16000000
RCC.SYSCLKFreq_VALUE=48000000
RCC.SYSCLKSource=RCC_SYSCLKSOURCE_PLLCLK
board=custom

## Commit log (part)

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2020-06-14 Added project goals
2020-06-19 Docs and info
2020-06-20 Started Romi 32u4 control board firmware
2020-06-21 Some basic information being sent over i2c comms
2020-06-21 Some fake tests added, cool support in Platformio for testing
2020-06-23 breaking out different tasks into testable modules
2020-06-23 Setup some test cases around odometry and kinematics
2020-06-24 Passing some odometry and kinematics tests
2020-06-26 Setup skeleton and test for PID control
2020-06-26 Not even a full PID controller and the robot is hitting its tests
2020-06-26 PID meeting some test targets
2020-06-26 First working python ROS node
2020-06-27 Pulled settings over to main project from tests, still not good PID values
2020-06-27 Driver can change LED values on control board
2020-06-27 Add low battery warning chime to give time to shutdown RPI before brown out
2020-06-27 Turn up timeout for twist commands
2020-06-27 Basic driver to brainstem setup
2020-06-27 Adding reporting of velocity back to brain
2020-06-28 Compute actual velocity given reading of wheel RPM
2020-06-28 Launch file with gamepad support
2020-06-28 Keyboard teleop loopback working
2020-06-28 Working test with joystick
2020-06-28 Wasn't reporting battery MV because it was added to i2c packet AFTER send
2020-06-28 Publishing what I have so far of odometry data
2020-06-29 Added lino pid submodule
2020-06-29 Missing some dependencies
